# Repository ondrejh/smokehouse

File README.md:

# SmokeHouse

The IOT smokehouse thermometer using standard web server as the interface.

## Thermometer HW

## DB scheme ##

## Next steps (HW / FW) ##

- [X] use device registration (unique id, key)
- [X] add the second thermocoupler
- [X] draw schematic
- [X] design pcb
- [ ] oversampling
- [ ] assemble prototypes

## Next steps (WEBI) ##

- [X] limit data table length
- [X] keep time distances between rows
- [ ] consolidate folders
- [ ] build better local webi
- [ ] build better server webi

## Next steps (all)

- [ ] update docu

## Install LAMP ##

https://gist.github.com/ondrejh/c1df59c4e6e8c8cb88a95b12bdac447b#file-lamp_install-md

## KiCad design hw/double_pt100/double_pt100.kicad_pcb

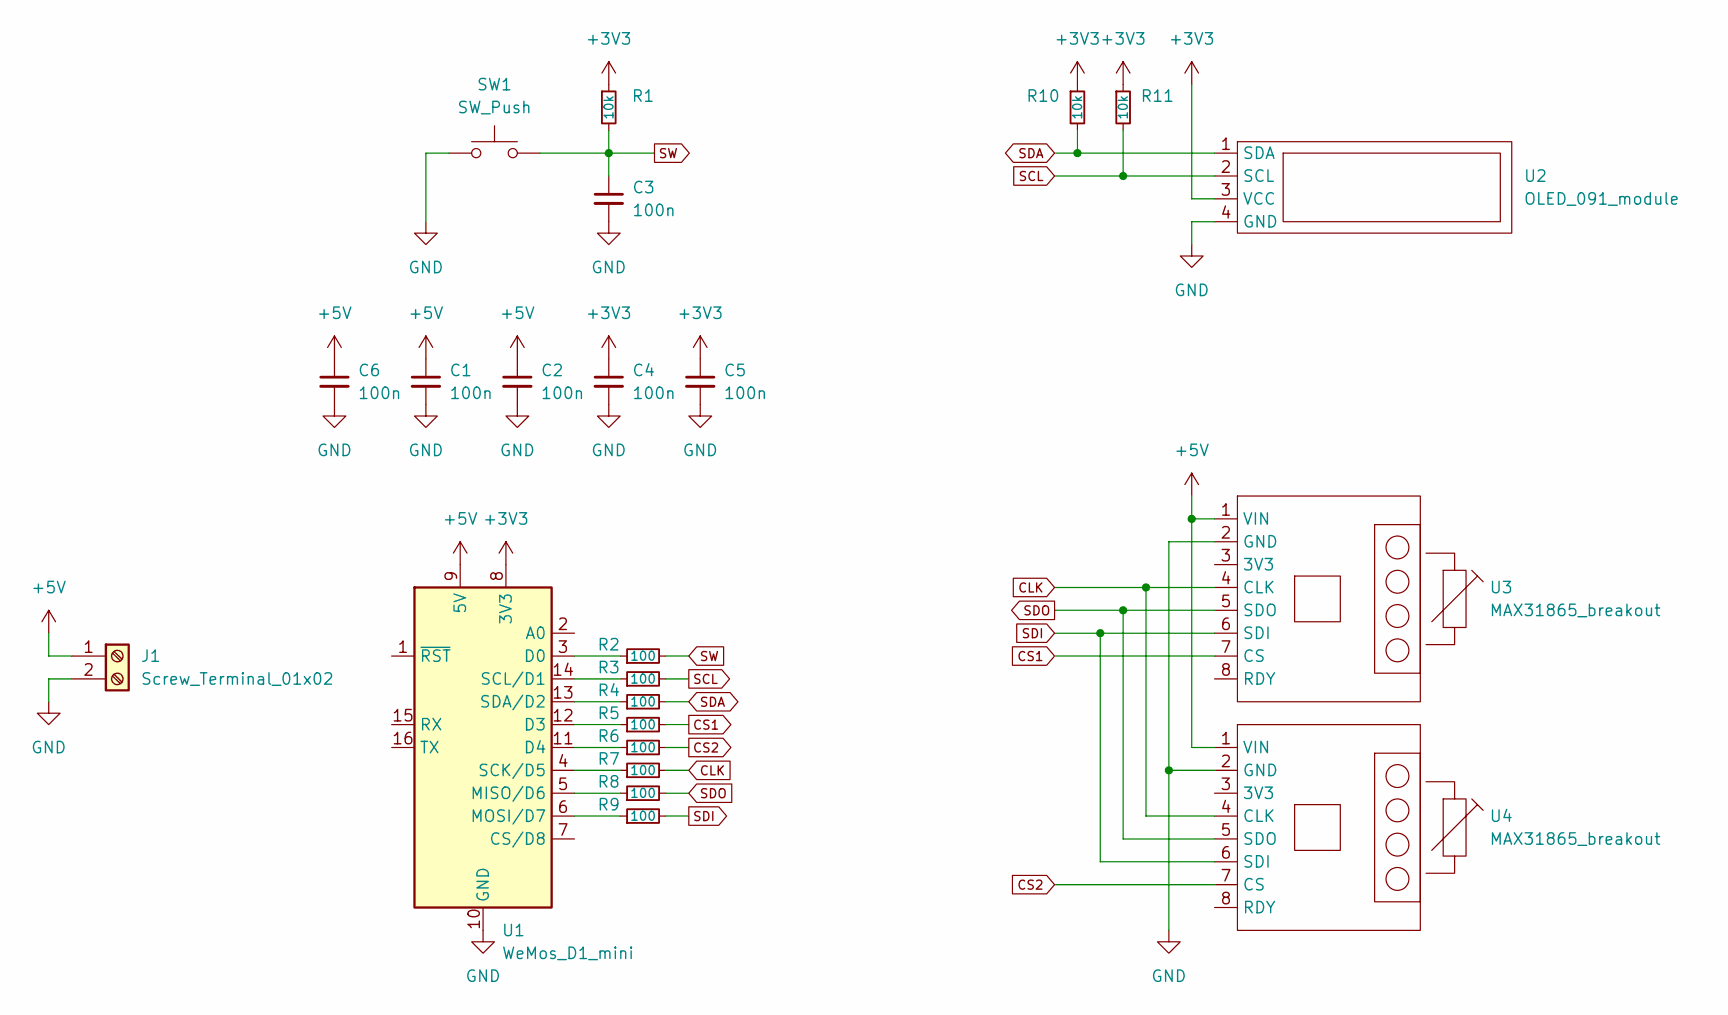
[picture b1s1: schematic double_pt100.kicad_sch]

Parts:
C1, C2, C3, C4, C5, C6: 100n; C_0603_1608Metric
J1: Screw_Terminal_01x02; TerminalBlock_Phoenix_PT-1,5-2-3.5-H_1x02_P3.50mm_Horizontal
R1, R10, R11: 10k; R_0603_1608Metric
R2, R3, R4, R5, R6, R7, R8, R9: 100; R_0603_1608Metric
SW1: SW_Push; SW_Push_1P1T_NO_CK_KSC6xxJ
U1: WeMos_D1_mini; WEMOS_D1_mini_light
U2: OLED_091_module
U3, U4: MAX31865_breakout; MAX31865_module

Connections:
+3V3: C4.1, C5.1, R1.1, R10.1, R11.1, U1.8 (3V3), U2.3 (VCC)
+5V: C1.1, C2.1, C6.1, J1.1, U1.9 (5V), U3.1 (VIN), U4.1 (VIN)
CLK: R7.2, U3.4 (CLK), U4.4 (CLK)
CS1: R5.2, U3.7 (CS)
CS2: R6.2, U4.7 (CS)
GND: C1.2, C2.2, C3.2, C4.2, C5.2, C6.2, J1.2, SW1.1, U1.10 (GND), U2.4 (GND), U3.2 (GND), U4.2 (GND)
unnamed: R2.1, U1.3 (D0)
unnamed: R3.1, U1.14 (SCL/D1)
unnamed: R4.1, U1.13 (SDA/D2)
unnamed: R5.1, U1.12 (D3)
unnamed: R6.1, U1.11 (D4)
unnamed: R7.1, U1.4 (SCK/D5)
unnamed: R8.1, U1.5 (MISO/D6)
unnamed: R9.1, U1.6 (MOSI/D7)
SCL: R3.2, R11.2, U2.2 (SCL)
SDA: R4.2, R10.2, U2.1 (SDA)
SDI: R9.2, U3.6 (SDI), U4.6 (SDI)
SDO: R8.2, U3.5 (SDO), U4.5 (SDO)
SW: C3.1, R1.2, R2.2, SW1.2

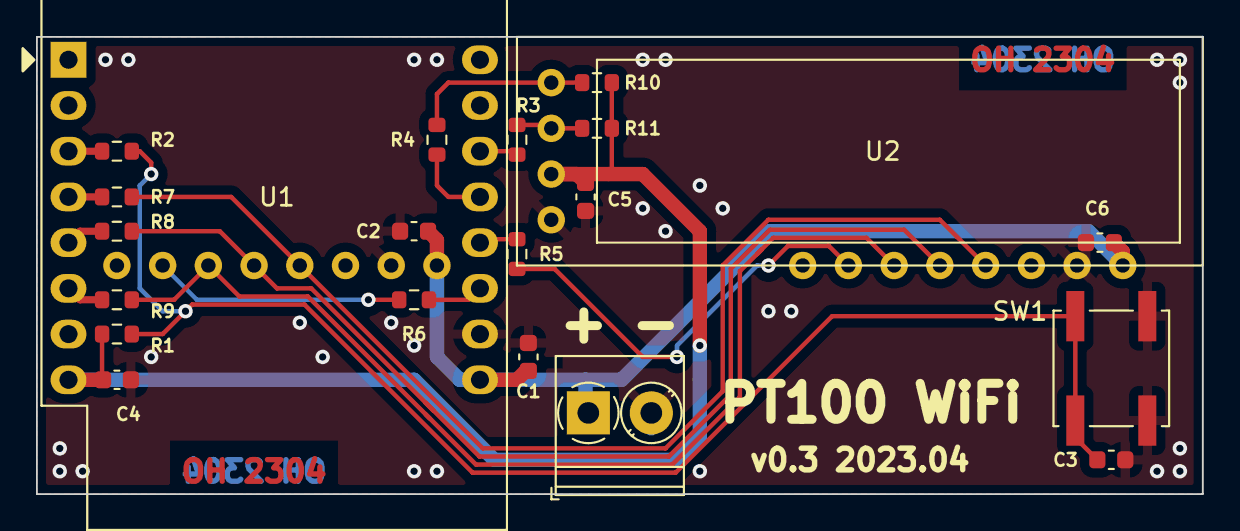
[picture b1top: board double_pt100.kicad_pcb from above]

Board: 2 copper layers, 64.8 x 25.4 mm, 23 parts (0 on the bottom side), 19 nets.

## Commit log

2020-12-07 sketch initial
2020-12-07 readme update
2020-12-08 webi - not yet, but the folder
2020-12-08 some installation hints
2020-12-08 todo list
2020-12-08 todo list (improved)
2020-12-10 basic form
2020-12-10 in (slow) progress
2020-12-12 simple data input
2020-12-13 post forms and tests
2020-12-13 json test form and input
2020-12-14 important note
2020-12-14 send json data
2020-12-14 mysql
2020-12-14 gototheworld
2020-12-15 register device into the database
2020-12-15 list devices
2020-12-15 todo update
2020-12-15 simple thermometer connected
2020-12-15 project cleanup
2020-12-16 ftp command list to simplify export
2020-12-16 allow change device name
2020-12-16 new scheme
2020-12-16 new sketch for th simple sensor
2020-12-21 not finished yet
2020-12-21 some changes
2020-12-21 show device form (not finished)
2020-12-24 lamp install improved
2020-12-24 different headers
2020-12-24 lamp install moved to gist
2021-01-22 device viewer
2021-01-22 y starts with 0
2021-01-22 time display formats
2021-02-19 return last values the device sent
2021-02-19 remote display
2021-05-04 schematic - not tested
2021-05-04 second sensor
2021-05-05 post debug
2021-05-05 double temp support
2021-05-05 display temperature source (1 / 2)
2023-01-28 test program with morse output
2023-01-31 first hw
2023-01-31 layout done
2023-02-01 gerbers to order the prototype
2023-02-03 pcb doc
2023-02-03 wrap web server example
2023-02-03 max31685 test ino moved to sketch dir
2023-02-04 button display cycler
2023-02-05 connecting display
2023-02-05 prepare for ap mode
2023-02-05 one read on loop only
2023-02-05 ap mode
2023-02-15 iBOM to ease assembly
2023-02-17 eeprom (emulated) and configuration
2023-02-22 basic webi
2023-02-22 webi source
2023-02-23 push data to server
2023-02-24 not secure connect
2023-02-25 limit table lenght
2023-02-25 readme update, remove debug symbols
2023-02-25 keep time distance between samples
2023-02-25 defoldering
2023-02-25 main sketch renamed to device
2023-02-25 removed secrets - all is configurable already
2023-02-26 avg 8 samples
2023-02-28 no wifi version of the device sketch
2023-03-03 temp page base
2023-03-04 locav webi update
2023-03-04 compiled with new webi
2023-03-04 server temp form
2023-03-11 keg scale device data input
2023-03-12 kegscale device input
2023-03-25 hw version 0.2 with alternative assembly
2023-04-09 evaulate disconnected sensor or broken adc, send null in the case
2023-04-09 no wifi alternative hw extra directory
2023-04-09 dir renamed
2023-04-09 yet another dir rename
2023-04-11 hw version mini
2024-01-20 some debug
2024-01-20 improved server data
2024-02-03 case
2024-02-03 http restapi endpoint
2024-02-03 testing dirrectory
2024-02-03 improved remote push timing
2024-02-04 display transfer icon while transfering data to server
2024-02-04 yet even better transfer icon
2024-02-04 display cycling debug
2024-02-04 data endpoint
2025-12-06 mqtt to settings
2025-12-06 ha mqtt, first success
2025-12-07 mqtt settings implemented in device
2025-12-07 binary
2026-01-14 debug - temperature display function
